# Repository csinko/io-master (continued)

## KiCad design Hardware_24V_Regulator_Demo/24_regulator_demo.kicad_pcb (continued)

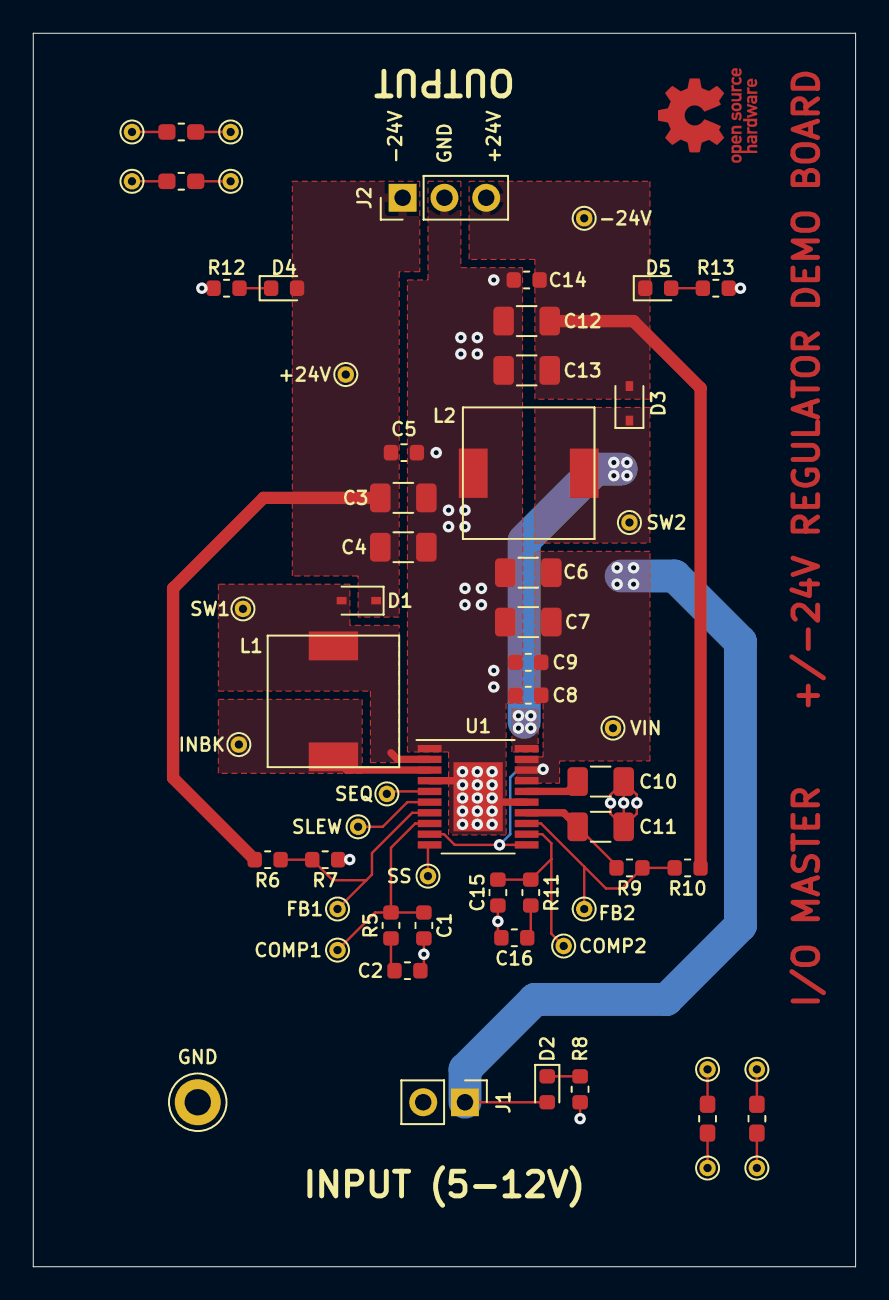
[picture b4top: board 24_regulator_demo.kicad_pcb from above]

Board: 2 copper layers, 50.0 x 75.0 mm, 61 parts (0 on the bottom side), 29 nets.

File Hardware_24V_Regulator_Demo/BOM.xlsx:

24V Regulator Demo Board - Populated Parts
Qty. | Refdes. | Description | Manufacturer | Manufacturer PN | Digikey PN | Unit Price | Extended Price
1.0 | PCB1 | bare pcb, 2 layer, 1 oz copper, green soldermask, 50x75mm | JLCPCB |  |  | 0.4 | 0.4
1.0 | C2 | 270p capacitor, ceramic, 50V 10%, X7R, 0603 | Samsung | CL10B271KB8NNNC | 1276-2019-1-ND | 0.1 | 0.1
1.0 | C8 | 0.1u capacitor, ceramic, 50V 10%, X7R, 0603 | Samsung | CL10B104KB8NNNL | 1276-CL10B104KB8NNNLCT-ND | 0.1 | 0.1
3.0 | C4, C7, C13 | 10u capacitor, ceramic, 50V 20%, X5R, 1206 | Samsung | CL31A106MBHNNNE | 1276-6736-1-ND | 0.3 | 0.9
2.0 | C10, C11 | 1u capacitor, ceramic, 50V 20%, X5R, 1206 | Samsung | CL31A106MBHNNNE | 1276-6736-1-ND | 0.3 | 0.6
1.0 | C16 | 0.22u capacitor, ceramic, 50V 10%, X5R, 0603 | Samsung | CL10A224KB8NNNC | 1276-1876-1-ND | 0.18 | 0.18
1.0 | D1 | schottky diode, Vf=0.62V, 30V 500mA, SOD-323 | ON Semi | NSR0530HT1G | NSR0530HT1GOSCT-ND | 0.16 | 0.16
2.0 | D2, D3 | green led, Vf=2V, 0603 | Wurth | 150060VS75000 | 732-4980-1-ND | 0.16 | 0.32
2.0 | D4, D5 | blue led, Vf=3.2V, 0603 | Wurth | 150060BS75000 | 732-4966-1-ND | 0.16 | 0.32
1.0 | J1 | 2 pin header, 0.1", vertical, through hole | Sullins | PREC002SAAN-RC | S1012EC-02-ND | 0.16 | 0.16
1.0 | J2 | 3 pin header, 0.1", vertical, through hole | Sullins | PREC003SAAN-RC | S1012EC-03-ND | 0.16 | 0.16
2.0 | L1, L2 | 15uH inductor, 3.5A rated, 4.4A saturation, shielded, smd | Murata | DD1217AS-H-150M=P3 | 490-13203-1-ND | 0.16 | 0.32
1.0 | R5 | 340K resistor, 1%, 1/10W, 0603 | Vishay Dale | CRCW0603340KFKEA | 541-340KHCT-ND | 0.1 | 0.1
1.0 | R6 | 3.09M resistor, 1%, 1/10W, 0603 | Vishay Dale | CRCW06033M09FKEA | 541-3.09MHCT-ND | 0.1 | 0.1
1.0 | R7 | 107K resistor, 1%, 1/10W, 0603 | Vishay Dale | CRCW0603107KFKEA | 541-107KHCT-ND | 0.1 | 0.1
3.0 | R8, R12, R13 | 10K resistor, 1%, 1/10W, 0603 | Vishay Dale | CRCW060310K0FKEA | 541-10.0KHCT-ND | 0.1 | 0.3
1.0 | R9 | 102K resistor, 1%, 1/10W, 0603 | Vishay Dale | CRCW0603102KFKEA | 541-102KHCT-ND | 0.1 | 0.1
1.0 | R10 | 3.16M resistor, 1%, 1/10W, 0603 | Vishay Dale | CRCW06033M16FKEA | 541-3.16MHCT-ND | 0.1 | 0.1
1.0 | R11 | 5.36K resistor, 1%, 1/10W, 0603 | Vishay Dale | CRCW06035K36FKEA | 541-5.36KHCT-ND | 0.1 | 0.1
1.0 | TP15 | multipurpose test point loop | Keystone | 5011 | 36-5011-ND | 0.35 | 0.35
1.0 | U1 | switching regulator, pos & neg output, 2.5-15V input, 20-TSSOP | Analog Devices | ADP5070AREZ | ADP5070AREZ-R7CT-ND | 6.1 | 6.1
 |  |  |  |  |  | BOM Total | 11.07

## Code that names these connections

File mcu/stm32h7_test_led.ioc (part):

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Mcu.Name=STM32H743ZITx
Mcu.Package=LQFP144
Mcu.UserName=STM32H743ZITx
PA0.GPIOParameters=GPIO_Label
PA0.GPIO_Label=IO_1_OUT
PA0.Signal=S_TIM2_CH1
PA1.GPIOParameters=GPIO_Label
PA1.GPIO_Label=IO_2_OUT
PA1.Signal=S_TIM5_CH2
PA10.GPIOParameters=GPIO_Label
PA10.GPIO_Label=UART_RXI
PA10.Signal=USART1_RX
PA11.GPIOParameters=GPIO_Label
PA11.GPIO_Label=USB_FS_DM
PA11.Signal=USB_OTG_FS_DM
PA12.GPIOParameters=GPIO_Speed,GPIO_PuPd,GPIO_Label,GPIO_Mode
PA12.GPIO_Label=USB_FS_DP
PA12.GPIO_Mode=GPIO_MODE_AF_PP
PA12.GPIO_PuPd=GPIO_NOPULL
PA12.GPIO_Speed=GPIO_SPEED_FREQ_LOW
PA12.Signal=USB_OTG_FS_DP
PA13\ (JTMS/SWDIO).GPIOParameters=GPIO_Label
PA13\ (JTMS/SWDIO).GPIO_Label=TMS/SWDIO
PA13\ (JTMS/SWDIO).Mode=JTAG_5_pins
PA13\ (JTMS/SWDIO).Signal=DEBUG_JTMS-SWDIO
PA14\ (JTCK/SWCLK).GPIOParameters=GPIO_Label
PA14\ (JTCK/SWCLK).GPIO_Label=TCK/SWDCLK
PA14\ (JTCK/SWCLK).Mode=JTAG_5_pins
PA14\ (JTCK/SWCLK).Signal=DEBUG_JTCK-SWCLK
PA15\ (JTDI).GPIOParameters=GPIO_Label
PA15\ (JTDI).GPIO_Label=TDI
PA15\ (JTDI).Mode=JTAG_5_pins
PA15\ (JTDI).Signal=DEBUG_JTDI
PA2.GPIOParameters=GPIO_Label
PA2.GPIO_Label=IO_3_OUT
PA2.Signal=S_TIM15_CH1
PA3.GPIOParameters=GPIO_Label
PA3.GPIO_Label=ULPI_D0
PA3.Signal=USB_OTG_HS_ULPI_D0
PA4.GPIOParameters=GPIO_Label
PA4.GPIO_Label=Vout_SETPOINT
PA4.Signal=COMP_DAC11_group
PA5.GPIOParameters=GPIO_Label
PA5.GPIO_Label=ULPI_CK
PA5.Signal=USB_OTG_HS_ULPI_CK
PA6.GPIOParameters=GPIO_Label
PA6.GPIO_Label=IO_6_PU
PA6.Signal=GPIO_Output
PA7.GPIOParameters=GPIO_Label
PA7.GPIO_Label=IO_8_OUT
PA7.Signal=S_TIM14_CH1
PA8.GPIOParameters=GPIO_Label
PA8.GPIO_Label=I2C_SCL
PA8.Signal=I2C3_SCL
PA9.GPIOParameters=GPIO_Label
PA9.GPIO_Label=UART_TXO
PA9.Signal=USART1_TX
PB0.GPIOParameters=GPIO_Label
PB0.GPIO_Label=ULPI_D1
PB0.Signal=USB_OTG_HS_ULPI_D1
PB1.GPIOParameters=GPIO_Label
PB1.GPIO_Label=ULPI_D2
PB1.Signal=USB_OTG_HS_ULPI_D2
PB10.GPIOParameters=GPIO_Label
PB10.GPIO_Label=ULPI_D3
PB10.Signal=USB_OTG_HS_ULPI_D3
PB11.GPIOParameters=GPIO_Label
PB11.GPIO_Label=ULPI_D4
PB11.Signal=USB_OTG_HS_ULPI_D4
PB12.GPIOParameters=GPIO_Label
PB12.GPIO_Label=ULPI_D5
PB12.Signal=USB_OTG_HS_ULPI_D5
PB13.GPIOParameters=GPIO_Label
PB13.GPIO_Label=ULPI_D6
PB13.Signal=USB_OTG_HS_ULPI_D6
PB14.GPIOParameters=PinState,GPIO_Label
PB14.GPIO_Label=IO_1_PU
PB14.PinState=GPIO_PIN_SET
PB14.Signal=GPIO_Output
PB15.GPIOParameters=GPIO_Label
PB15.GPIO_Label=IO_1_PD_N
PB15.Signal=GPIO_Output
PB2.GPIOParameters=PinState,GPIO_Label
PB2.GPIO_Label=IO_6_PD_N
PB2.PinState=GPIO_PIN_SET
PB2.Signal=GPIO_Output
PB3\ (JTDO/TRACESWO).GPIOParameters=GPIO_Label
PB3\ (JTDO/TRACESWO).GPIO_Label=TDO/SWO
PB3\ (JTDO/TRACESWO).Mode=JTAG_5_pins
PB3\ (JTDO/TRACESWO).Signal=DEBUG_JTDO-SWO
PB4\ (NJTRST).GPIOParameters=GPIO_Label
PB4\ (NJTRST).GPIO_Label=nRESET
PB4\ (NJTRST).Mode=JTAG_5_pins
PB4\ (NJTRST).Signal=DEBUG_JTRST
PB5.GPIOParameters=GPIO_Label
PB5.GPIO_Label=ULPI_D7
PB5.Signal=USB_OTG_HS_ULPI_D7
PB6.GPIOParameters=GPIO_Label
PB6.GPIO_Label=IO_4_PU
PB6.Signal=GPIO_Output
PB7.GPIOParameters=GPIO_Label
PB7.GPIO_Label=IO_5_OUT
PB7.Signal=S_TIM4_CH2
PB8.GPIOParameters=GPIO_Label
PB8.GPIO_Label=IO_6_OUT
PB8.Signal=S_TIM16_CH1
PC0.GPIOParameters=GPIO_Label
PC0.GPIO_Label=ULPI_STP
PC0.Signal=USB_OTG_HS_ULPI_STP
PC1.GPIOParameters=PinState,GPIO_Label
PC1.GPIO_Label=IO_7_PU
PC1.PinState=GPIO_PIN_SET
PC1.Signal=GPIO_Output
PC10.GPIOParameters=GPIO_Label
PC10.GPIO_Label=IO_3_4_TERM_N
PC10.Signal=GPIO_Output
PC11.GPIOParameters=GPIO_Label
PC11.GPIO_Label=IO_3&4_DIFF
PC11.Signal=GPIO_Output
PC12.GPIOParameters=PinState,GPIO_Label
PC12.GPIO_Label=IO_4_PD_N
PC12.PinState=GPIO_PIN_SET
PC12.Signal=GPIO_Output
PC13.GPIOParameters=PinState,GPIO_Label
PC13.GPIO_Label=IO_7&8_DIFF
PC13.PinState=GPIO_PIN_SET
PC13.Signal=GPIO_Output
PC14-OSC32_IN\ (OSC32_IN).GPIOParameters=GPIO_Label
PC14-OSC32_IN\ (OSC32_IN).GPIO_Label=IO_5_6_DIFF
PC14-OSC32_IN\ (OSC32_IN).Signal=GPIO_Output
PC15-OSC32_OUT\ (OSC32_OUT).GPIOParameters=PinState,GPIO_Label
PC15-OSC32_OUT\ (OSC32_OUT).GPIO_Label=IO_5&6_TERM_N
PC15-OSC32_OUT\ (OSC32_OUT).PinState=GPIO_PIN_SET
PC15-OSC32_OUT\ (OSC32_OUT).Signal=GPIO_Output
PC2_C.GPIOParameters=GPIO_Label
PC2_C.GPIO_Label=ULPI_DIR
PC2_C.Signal=USB_OTG_HS_ULPI_DIR
PC3_C.GPIOParameters=GPIO_Label
PC3_C.GPIO_Label=ULPI_NXT
PC3_C.Signal=USB_OTG_HS_ULPI_NXT
PC4.GPIOParameters=GPIO_Label
PC4.GPIO_Label=IO_7_PD_N
PC4.Signal=GPIO_Output
PC5.GPIOParameters=PinState,GPIO_Label
PC5.GPIO_Label=IO_8_PU
PC5.PinState=GPIO_PIN_SET
PC5.Signal=GPIO_Output
PC6.GPIOParameters=GPIO_Label
PC6.GPIO_Label=IO_4_OUT
PC6.Signal=S_TIM3_CH1
PC7.GPIOParameters=GPIO_Label
PC7.GPIO_Label=IO_8_PD_N
PC7.Signal=GPIO_Output
PC8.GPIOParameters=PinState,GPIO_Label
PC8.GPIO_Label=IO_7_8_TERM_N
PC8.PinState=GPIO_PIN_SET
PC8.Signal=GPIO_Output
PC9.GPIOParameters=GPIO_Label
PC9.GPIO_Label=I2C_SDA
PC9.Signal=I2C3_SDA
PD0.GPIOParameters=GPIO_Label
PD0.GPIO_Label=IO_1_OUT
PD0.Signal=GPIO_Output
PD1.GPIOParameters=GPIO_Label
PD1.GPIO_Label=IO_2_OUT
PD1.Signal=GPIO_Output
PD10.GPIOParameters=PinState,GPIO_Label
PD10.GPIO_Label=IO_3_TRIS_N
PD10.PinState=GPIO_PIN_SET
PD10.Signal=GPIO_Output
PD11.GPIOParameters=PinState,GPIO_Label
PD11.GPIO_Label=IO_4_TRIS_N
PD11.PinState=GPIO_PIN_SET
PD11.Signal=GPIO_Output
PD12.GPIOParameters=PinState,GPIO_Label
PD12.GPIO_Label=IO_5_TRIS_N
PD12.PinState=GPIO_PIN_SET
PD12.Signal=GPIO_Output
PD13.GPIOParameters=PinState,GPIO_Label
PD13.GPIO_Label=IO_6_TRIS_N
PD13.PinState=GPIO_PIN_SET
PD13.Signal=GPIO_Output
PD14.GPIOParameters=PinState,GPIO_Label
PD14.GPIO_Label=IO_7_TRIS_N
PD14.PinState=GPIO_PIN_SET
PD14.Signal=GPIO_Output
PD15.GPIOParameters=PinState,GPIO_Label
PD15.GPIO_Label=IO_8_TRIS_N
PD15.PinState=GPIO_PIN_SET
PD15.Signal=GPIO_Output
PD2.GPIOParameters=GPIO_Label
PD2.GPIO_Label=IO_3_OUT
PD2.Signal=GPIO_Output
PD3.GPIOParameters=GPIO_Label
PD3.GPIO_Label=IO_4_OUT
PD3.Signal=GPIO_Output
PD4.GPIOParameters=GPIO_Label
PD4.GPIO_Label=IO_5_OUT
PD4.Signal=GPIO_Output
PD5.GPIOParameters=GPIO_Label
PD5.GPIO_Label=IO_6_OUT
PD5.Signal=GPIO_Output
PD6.GPIOParameters=GPIO_Label
PD6.GPIO_Label=IO_7_OUT
PD6.Signal=GPIO_Output
PD7.GPIOParameters=GPIO_Label
PD7.GPIO_Label=IO_8_OUT
PD7.Signal=GPIO_Output
PD8.GPIOParameters=PinState,GPIO_Label
PD8.GPIO_Label=IO_1_TRIS_N
PD8.PinState=GPIO_PIN_SET
PD8.Signal=GPIO_Output
PD9.GPIOParameters=PinState,GPIO_Label
PD9.GPIO_Label=IO_2_TRIS_N
PD9.PinState=GPIO_PIN_SET
PD9.Signal=GPIO_Output
PE10.GPIOParameters=GPIO_Label
PE10.GPIO_Label=IO_3_IN
PE10.Signal=GPIO_Input
PE11.GPIOParameters=GPIO_Label
PE11.GPIO_Label=IO_4_IN
PE11.Signal=GPIO_Input
PE12.GPIOParameters=GPIO_Label
PE12.GPIO_Label=IO_5_IN
PE12.Signal=GPIO_Input
PE13.GPIOParameters=GPIO_Label
PE13.GPIO_Label=IO_6_IN
PE13.Signal=GPIO_Input
PE14.GPIOParameters=GPIO_Label
PE14.GPIO_Label=IO_7_IN
PE14.Signal=GPIO_Input
PE15.GPIOParameters=GPIO_Label
PE15.GPIO_Label=IO_8_IN
PE15.Signal=GPIO_Input
PE8.GPIOParameters=GPIO_Label
PE8.GPIO_Label=IO_1_IN
PE8.Signal=GPIO_Input
PE9.GPIOParameters=GPIO_Label
PE9.GPIO_Label=IO_2_IN
PE9.Signal=GPIO_Input
PF0.GPIOParameters=GPIO_Label
PF0.GPIO_Label=STATUS_R
PF0.Signal=GPIO_Output
PF1.GPIOParameters=GPIO_Label
PF1.GPIO_Label=STATUS_G
PF1.Signal=GPIO_Output
PF2.GPIOParameters=GPIO_Label
PF2.GPIO_Label=STATUS_B
PF2.Signal=GPIO_Output
PG0.GPIOParameters=GPIO_Label
PG0.GPIO_Label=IO_5_PU
PG0.Signal=GPIO_Output
PG1.GPIOParameters=PinState,GPIO_Label
PG1.GPIO_Label=IO_5_PD_N
PG1.PinState=GPIO_PIN_SET
PG1.Signal=GPIO_Output
PG2.GPIOParameters=GPIO_Label
PG2.GPIO_Label=IO_1_2_DIFF
PG2.Signal=GPIO_Output
PG3.GPIOParameters=PinState,GPIO_Label
PG3.GPIO_Label=IO_1_2_TERM_N
PG3.PinState=GPIO_PIN_SET
PG3.Signal=GPIO_Output
PG4.GPIOParameters=GPIO_Label
PG4.GPIO_Label=IO_2_PD_N
PG4.Signal=GPIO_Output
PG5.GPIOParameters=PinState,GPIO_Label
PG5.GPIO_Label=IO_2_PU
PG5.PinState=GPIO_PIN_SET
PG5.Signal=GPIO_Output
PG6.GPIOParameters=GPIO_Speed,PinState,GPIO_PuPd,GPIO_Label,GPIO_ModeDefaultOutputPP
PG6.GPIO_Label=IO_3_PU
PG6.GPIO_ModeDefaultOutputPP=GPIO_MODE_OUTPUT_PP
PG6.GPIO_PuPd=GPIO_NOPULL
PG6.GPIO_Speed=GPIO_SPEED_FREQ_LOW
PG6.PinState=GPIO_PIN_RESET
PG6.Signal=GPIO_Output
PG7.GPIOParameters=PinState,GPIO_Label
PG7.GPIO_Label=IO_3_PD_N
PG7.PinState=GPIO_PIN_SET
PG7.Signal=GPIO_Output
PH0-OSC_IN\ (PH0).GPIOParameters=GPIO_Label
PH0-OSC_IN\ (PH0).GPIO_Label=OSC_IN
PH0-OSC_IN\ (PH0).Mode=HSE-External-Oscillator
PH0-OSC_IN\ (PH0).Signal=RCC_OSC_IN
PH1-OSC_OUT\ (PH1).Mode=HSE-External-Oscillator
PH1-OSC_OUT\ (PH1).Signal=RCC_OSC_OUT
RCC.HSE_VALUE=17000000
RCC.SYSCLKFreq_VALUE=480000000
RCC.SYSCLKSource=RCC_SYSCLKSOURCE_PLLCLK
RCC.SYSCLKSourceVirtual=RCC_SYSCLKSOURCE_PLLCLK
board=NUCLEO-H743ZI
boardIOC=true

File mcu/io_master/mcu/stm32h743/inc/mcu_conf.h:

#ifndef __IO_MASTER_MCU_CONF_H
#define __IO_MASTER_MCU_CONF_H
#ifdef __cplusplus
extern "C" {
#endif

#include "stm32h743xx.h"
//DMA Buffer Size Definitions
#define DMA_OUTPUT_BUF_MAX_SIZE 1024 ///< A max size so the buffer memory domain doesn't fill up
#define DMA_WRITE_BUF_MIN_ADDR ((void*) 0x30000000) ///< The starting address of the DMA write buffer
#define DMA_WRITE_BUF_MAX_ADDR ((void*) DMA_WRITE_BUF_MIN_ADDR + DMA_OUTPUT_BUF_MAX_SIZE) ///< The ending address of the DMA Write buffer
#define OUTPUT_BUF_QUEUE_MAX_SIZE 10 ///< The size of the DMA output buffer queue

//UART Buffer Size Definitions
#define UART_TX_BUF_QUEUE_MAX_SIZE 10 ///< The size of the UART output buffer queue
#define UART_RX_BUF_QUEUE_MAX_SIZE 10 ///< The size of the UART input buffer queue

//IO Software Pin Definitions
#define IO_PIN_GPIO_INPUT_PORT GPIOE
#define IO_PIN_GPIO_INPUT_OFFSET 1
#define IO_PIN_1_INPUT 8
#define IO_PIN_2_INPUT 9
#define IO_PIN_3_INPUT 10
#define IO_PIN_4_INPUT 11

#define IO_PIN_GPIO_OUTPUT_PORT GPIOD
#define IO_PIN_GPIO_OUTPUT_OFFSET 0
#define IO_PIN_1_OUTPUT 0
#define IO_PIN_2_OUTPUT 1
#define IO_PIN_3_OUTPUT 2
#define IO_PIN_4_OUTPUT 3

//IO Input
#define IO_1_IN_GPIO_Port GPIOE
#define IO_1_IN_Pin GPIO_PIN_8

#define IO_2_IN_GPIO_Port GPIOE
#define IO_2_IN_Pin GPIO_PIN_9

#define IO_3_IN_GPIO_Port GPIOE
#define IO_3_IN_Pin GPIO_PIN_10

#define IO_4_IN_GPIO_Port GPIOE
#define IO_4_IN_Pin GPIO_PIN_11

#ifdef IOM_8_IO_PINS
#define IO_5_IN_GPIO_Port GPIOE
#define IO_5_IN_Pin GPIO_PIN_12

#define IO_6_IN_GPIO_Port GPIOE
#define IO_6_IN_Pin GPIO_PIN_13

#define IO_7_IN_GPIO_Port GPIOE
#define IO_7_IN_Pin GPIO_PIN_14

#define IO_8_IN_GPIO_Port GPIOE
#define IO_8_IN_Pin GPIO_PIN_15
#endif

//IO Timer OUT
#define IO_1_CLK_GPIO_Port GPIOA
#define IO_1_CLK_Pin GPIO_PIN_0

#define IO_2_CLK_GPIO_Port GPIOA
#define IO_2_CLK_Pin GPIO_PIN_1

#define IO_3_CLK_GPIO_Port GPIOA
#define IO_3_CLK_Pin GPIO_PIN_2

#define IO_4_CLK_GPIO_Port GPIOC
#define IO_4_CLK_Pin GPIO_PIN_6

#ifdef IOM_8_IO_PINS
#define IO_5_CLK_GPIO_Port GPIOB
#define IO_5_CLK_Pin GPIO_PIN_7

#define IO_6_CLK_GPIO_Port GPIOB
#define IO_6_CLK_Pin GPIO_PIN_8

#define IO_7_CLK_GPIO_Port GPIOB
#define IO_7_CLK_Pin GPIO_PIN_9

#define IO_8_CLK_GPIO_Port GPIOA
#define IO_8_CLK_Pin GPIO_PIN_7
#endif

//IO Digital OUT
#define IO_1_OUT_GPIO_Port GPIOD
#define IO_1_OUT_Pin GPIO_PIN_0

#define IO_2_OUT_GPIO_Port GPIOD
#define IO_2_OUT_Pin GPIO_PIN_1

#define IO_3_OUT_GPIO_Port GPIOD
#define IO_3_OUT_Pin GPIO_PIN_2

#define IO_4_OUT_GPIO_Port GPIOD
#define IO_4_OUT_Pin GPIO_PIN_3

#ifdef IOM_8_IO_PINS
#define IO_5_OUT_GPIO_Port GPIOD
#define IO_5_OUT_Pin GPIO_PIN_4

#define IO_6_OUT_GPIO_Port GPIOD
#define IO_6_OUT_Pin GPIO_PIN_5

#define IO_7_OUT_GPIO_Port GPIOD
#define IO_7_OUT_Pin GPIO_PIN_6

#define IO_8_OUT_GPIO_Port GPIOD
#define IO_8_OUT_Pin GPIO_PIN_7
#endif


// Differential Enable Pins
#define IO_1_2_DIFF_GPIO_Port GPIOG
#define IO_1_2_DIFF_Pin GPIO_PIN_2

#define IO_3_4_DIFF_GPIO_Port GPIOC
#define IO_3_4_DIFF_Pin GPIO_PIN_11

#ifdef IOM_8_IO_PINS
#define IO_5_6_DIFF_GPIO_Port GPIOC
#define IO_5_6_DIFF_Pin GPIO_PIN_14

#define IO_7_8_DIFF_GPIO_Port GPIOC
#define IO_7_8_DIFF_Pin GPIO_PIN_13
#endif

// Termination Pins (Active Low)
#define IO_1_2_TERM_N_GPIO_Port GPIOG
#define IO_1_2_TERM_N_Pin GPIO_PIN_3

#define IO_3_4_TERM_N_GPIO_Port GPIOC
#define IO_3_4_TERM_N_Pin GPIO_PIN_10

#ifdef IOM_8_IO_PINS
#define IO_5_6_TERM_N_GPIO_Port GPIOC
#define IO_5_6_TERM_N_Pin GPIO_PIN_15

#define IO_7_8_TERM_N_GPIO_Port GPIOC
#define IO_7_8_TERM_N_Pin GPIO_PIN_8
#endif

// Pullup Pins
#define IO_1_PU_GPIO_Port GPIOB
#define IO_1_PU_Pin GPIO_PIN_14

#define IO_2_PU_GPIO_Port GPIOG
#define IO_2_PU_Pin GPIO_PIN_5

#define IO_3_PU_GPIO_Port GPIOG
#define IO_3_PU_Pin GPIO_PIN_6

#define IO_4_PU_GPIO_Port GPIOB
#define IO_4_PU_Pin GPIO_PIN_6

#ifdef IOM_8_IO_PINS
#define IO_5_PU_GPIO_Port GPIOG
#define IO_5_PU_Pin GPIO_PIN_0

#define IO_6_PU_GPIO_Port GPIOA
#define IO_6_PU_Pin GPIO_PIN_6

#define IO_7_PU_GPIO_Port GPIOC
#define IO_7_PU_Pin GPIO_PIN_1

#define IO_8_PU_GPIO_Port GPIOC
#define IO_8_PU_Pin GPIO_PIN_5
#endif

//Pulldown Pins (Active Low)
#define IO_1_PD_N_GPIO_Port GPIOB
#define IO_1_PD_N_Pin GPIO_PIN_15

#define IO_2_PD_N_GPIO_Port GPIOG
#define IO_2_PD_N_Pin GPIO_PIN_4

#define IO_3_PD_N_GPIO_Port GPIOG
#define IO_3_PD_N_Pin GPIO_PIN_7

#define IO_4_PD_N_GPIO_Port GPIOC
#define IO_4_PD_N_Pin GPIO_PIN_12

#ifdef IOM_8_IO_PINS
#define IO_5_PD_N_GPIO_Port GPIOG
#define IO_5_PD_N_Pin GPIO_PIN_1

#define IO_6_PD_N_GPIO_Port GPIOB
#define IO_6_PD_N_Pin GPIO_PIN_2

#define IO_7_PD_N_GPIO_Port GPIOC
#define IO_7_PD_N_Pin GPIO_PIN_4

#define IO_8_PD_N_GPIO_Port GPIOC
#define IO_8_PD_N_Pin GPIO_PIN_7
#endif

//Tristate Pin (Active Low)
#define IO_1_TRIS_N_GPIO_Port GPIOD
#define IO_1_TRIS_N_Pin GPIO_PIN_8

#define IO_2_TRIS_N_GPIO_Port GPIOD
#define IO_2_TRIS_N_Pin GPIO_PIN_9

#define IO_3_TRIS_N_GPIO_Port GPIOD
#define IO_3_TRIS_N_Pin GPIO_PIN_10

#define IO_4_TRIS_N_GPIO_Port GPIOD
#define IO_4_TRIS_N_Pin GPIO_PIN_11

#ifdef IOM_8_IO_PINS
#define IO_5_TRIS_N_GPIO_Port GPIOD
#define IO_5_TRIS_N_Pin GPIO_PIN_12

#define IO_6_TRIS_N_GPIO_Port GPIOD
#define IO_6_TRIS_N_Pin GPIO_PIN_13

#define IO_7_TRIS_N_GPIO_Port GPIOD
#define IO_7_TRIS_N_Pin GPIO_PIN_14

#define IO_8_TRIS_N_GPIO_Port GPIOD
#define IO_8_TRIS_N_Pin GPIO_PIN_15
#endif

//Status LEDs
#define STATUS_R_GPIO_Port GPIOF
#define STATUS_R_Pin GPIO_PIN_1

#define STATUS_G_GPIO_Port GPIOF
#define STATUS_G_Pin GPIO_PIN_2

#define STATUS_B_GPIO_Port GPIOF
#define STATUS_B_Pin GPIO_PIN_0

//External Crystal Input
#define OSC_IN_GPIO_Port GPIOH
#define OSC_IN_Pin GPIO_PIN_0

//ULPI USB Interface
#define ULPI_STP_GPIO_Port GPIOC
#define ULPI_STP_Pin GPIO_PIN_0

#define ULPI_DIR_GPIO_Port GPIOC
#define ULPI_DIR_Pin GPIO_PIN_2

#define ULPI_NXT_GPIO_Port GPIOC
#define ULPI_NXT_Pin GPIO_PIN_3

#define ULPI_CK_GPIO_Port GPIOA
#define ULPI_CK_Pin GPIO_PIN_5

#define ULPI_D0_GPIO_Port GPIOA
#define ULPI_D0_Pin GPIO_PIN_3

#define ULPI_D1_GPIO_Port GPIOB
#define ULPI_D1_Pin GPIO_PIN_0

#define ULPI_D2_GPIO_Port GPIOB
#define ULPI_D2_Pin GPIO_PIN_1

#define ULPI_D3_GPIO_Port GPIOB
#define ULPI_D3_Pin GPIO_PIN_10

#define ULPI_D4_GPIO_Port GPIOB
#define ULPI_D4_Pin GPIO_PIN_11

#define ULPI_D5_GPIO_Port GPIOB
#define ULPI_D5_Pin GPIO_PIN_12

#define ULPI_D6_GPIO_Port GPIOB
#define ULPI_D6_Pin GPIO_PIN_13

#define ULPI_D7_GPIO_Port GPIOB
#define ULPI_D7_Pin GPIO_PIN_5

//DAC Output To Regulator
#define Vout_SETPOINT_GPIO_Port GPIOA
#define Vout_SETPOINT_Pin GPIO_PIN_4

//I2C (DAC?)
#define I2C_SDA_GPIO_Port GPIOC
#define I2C_SDA_Pin GPIO_PIN_9

#define I2C_SCL_GPIO_Port GPIOA
#define I2C_SCL_Pin GPIO_PIN_8

//Debug UART
#define UART_TXO_GPIO_Port GPIOA
#define UART_TXO_Pin GPIO_PIN_9

#define UART_RXI_GPIO_Port GPIOA
#define UART_RXI_Pin GPIO_PIN_10

//USB FS
#define USB_FS_DM_GPIO_Port GPIOA
#define USB_FS_DM_Pin GPIO_PIN_11

#define USB_FS_DP_GPIO_Port GPIOA
#define USB_FS_DP_Pin GPIO_PIN_12

//SWD (Unused)
#define TMS_SWDIO_GPIO_Port GPIOA
#define TMS_SWDIO_Pin GPIO_PIN_13

#define TCK_SWDCLK_GPIO_Port GPIOA
#define TCK_SWDCLK_Pin GPIO_PIN_14

#define TDI_GPIO_Port GPIOA
#define TDI_Pin GPIO_PIN_15

#define TDO_SWO_GPIO_Port GPIOB
#define TDO_SWO_Pin GPIO_PIN_3

#define nRESET_GPIO_Port GPIOB
#define nRESET_Pin GPIO_PIN_4

#ifdef __cplusplus
}
#endif
#endif

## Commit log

2019-09-16 Add subsystems to README
2019-10-17 Add MCU test code and project folder structure
2019-10-17 Add Windows script for running OpenOCD
2019-10-30 Add hardware v0 basic schematic
2019-10-30 LED usb test
2019-10-31 Add +/-24V regulator design
2019-11-06 Add 24V regulator demo board
2019-11-07 Add device config demo board
2019-11-07 Clean up 24v regulator demo board
2019-11-07 Clean up device config demo board
2019-11-07 Add level shifter demo board
2019-11-07 Update KiCAD symbol library
2019-11-07 Remove unnecessary footprint position file
2019-11-07 Add level shifter demo board BOM
2019-11-11 WIP with TIM1
2019-11-11 Update device config demo board fab drawing
2019-11-12 Add support for DMA on GPIOF (working)
2019-11-14 add support to control i2c for power rails
2019-11-14 Add gui
2019-11-14 add support to write to individual dac channels
2019-11-14 add delay between commands
2020-01-30 add configuration commands for mcu
2020-02-04 Clean up files
2020-02-04 Add v1 schematic design
2020-02-05 Add power changeover circuit, fix minor issues
2020-02-05 Replace switches U14 and U31 with higher voltage part
2020-02-05 Change barrel jack to cheaper part, add footprint
2020-02-05 Add custom footprints for crystals, leds, inductors, etc.
2020-02-07 Assign footprints, fix minor schematic issues
2020-02-07 Add PTC fuses on Vin and Vout
2020-02-08 Remove extra caps C18 and C21 on VDDA pin
2020-02-10 Add C18 and C21 0.1u decoupling caps, fix minor issues
2020-02-10 Add 2x5 pin header footprint w/ alternate numbering
2020-02-13 Update microcontroller pin assignments
2020-02-13 Add v1.0 PCB layout
2020-02-20 Add template code for outputting data, reorganize file structure
2020-02-20 Remove some of the auto gen templating comments as code generation is no longer needed
2020-02-20 add congiuration code
2020-02-20 Move files to match folder structure
2020-02-20 Move pin definitions for mcu_conf.h
2020-02-20 organize mcu_conf.h pin definitions
2020-02-20 Add interface files for core MCU functions and init functions
2020-02-20 Add GPIO Init Function
2020-02-20 Add init functions for DMA and TIM8
2020-02-20 add init function for dac
2020-02-20 Add init function for USB, add new C files to Makefile, remove usb_device files
2020-02-20 Add updated GUI code
2020-02-20 "merge main.c"
2020-02-22 Clean device initialization header files, organize GPIO pin initialization
2020-02-25 Restructure code so that it compiles
2020-02-26 Add I2C Intiialization
2020-02-27 Add initialization for UART interface
2020-02-27 Add support for UART and logging
2020-02-27 add windows config for vscode
2020-02-27 Add openocd command to makefile
2020-02-27 Fix issues with GPIO outputs causing dev board to freeze. Blinking LED test on STATUS_R output
2020-02-29 Add queueing system for UART TX
2020-03-01 Add UART RX command and parsing command structure
2020-03-03 Clean up command code, confirm pin state configuration works for IO 1
2020-03-03 Added Custom Packet GUI
2020-03-03 add io dac addresses
2020-03-03 Update clocks and interfaces for real board
2020-03-03 Finish up DAC config code for actual board
2020-03-03 rescaled write MCU DAC
2020-03-03 Add setPinStates command support
2020-03-03 Added A Pin select for SPI. Custom Packet also updated to be more customizeable
2020-03-05 Add timer initialization for clock outputs
2020-03-05 3/4/2020 Added Code to send characters via ascii and ordered according to standards
2020-03-05 Some Changes Made
2020-03-05 Minor Changes
2020-03-05 Get Output somewhat functional
2020-03-05 misc fixes
2020-03-05 Working SPI
2020-03-07 Improve clock syncing for sending data
2020-03-07 SPI works for first message only but it works so im committing this. This is a monumental software revision.
2020-03-07 Sending commands works well now
2020-03-07 Add timer initialiation to drive low
2020-03-07 Fix Output Idle States and DMA output
2020-03-10 Initial commit of python module for io_master_commands
2020-04-24 Rewrite main loop to include machine states
2020-04-25 Add v1.0 BOM
